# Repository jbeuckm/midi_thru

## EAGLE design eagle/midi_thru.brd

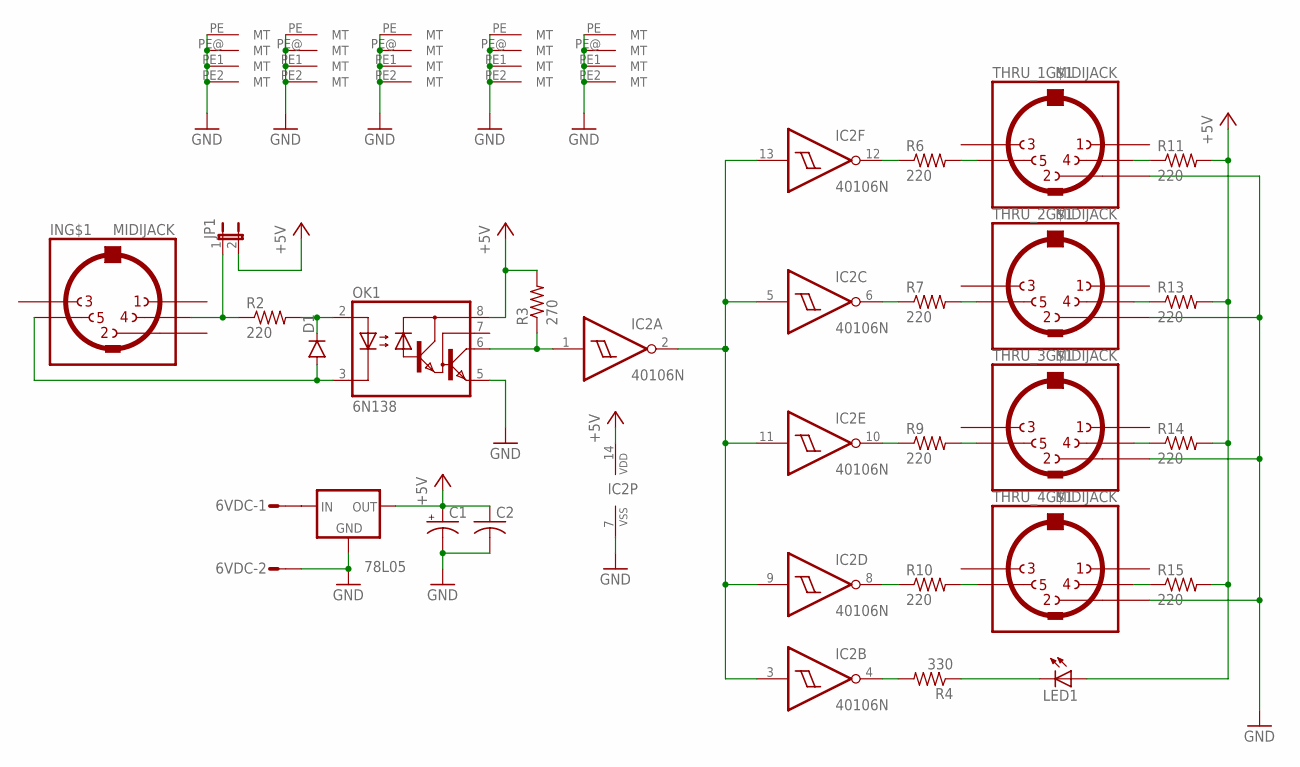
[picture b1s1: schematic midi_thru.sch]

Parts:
6VDC: S02P
78L05: 79LXX
C1: CPOL-USB45181A; B45181A
C2: C-US025-024X044; C025-024X044
D1: DIODE1N4148; DIODE-1N4148
IC2: 40106N; DIL14
IN: MIDIJACK; CP-2350
JP1: JP1E; JP1
LED1: LED5MM
OK1: 6N138; DIL08
R2, R6, R7, R9, R10, R11, R13, R14, R15: 220; 0207/7
R3: 270; 0207/7
R4: 330; 0207/7
THRU_1, THRU_2, THRU_3, THRU_4: MIDIJACK; CP-2350

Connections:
+5V: 78L05.OUT, C1.+, C2.1, IC2.14 (VDD), JP1.2, LED1.A, OK1.8 (VCC), R3.2, R11.2, R13.2, R14.2, R15.2
GND: 6VDC.2, 78L05.GND, C1.-, C2.2, IC2.7 (VSS), IN.PE (MT), IN.PE1 (MT), IN.PE2 (MT), IN.PE@ (MT), OK1.5 (GND), THRU_1.2, THRU_1.PE (MT), THRU_1.PE1 (MT), THRU_1.PE2 (MT), THRU_1.PE@ (MT), THRU_2.2, THRU_2.PE (MT), THRU_2.PE1 (MT), THRU_2.PE2 (MT), THRU_2.PE@ (MT), THRU_3.2, THRU_3.PE (MT), THRU_3.PE1 (MT), THRU_3.PE2 (MT), THRU_3.PE@ (MT), THRU_4.2, THRU_4.PE (MT), THRU_4.PE1 (MT), THRU_4.PE2 (MT), THRU_4.PE@ (MT)
unnamed: 6VDC.1, 78L05.IN
unnamed: IC2.4 (O), R4.2
unnamed: D1.A, IN.5, OK1.3 (C)
unnamed: LED1.K (C), R4.1
unnamed: IC2.8 (O), R10.1
unnamed: IN.4, JP1.1, R2.1
unnamed: D1.C, OK1.2 (A), R2.2
unnamed: IC2.10 (O), R9.1
unnamed: IC2.12 (O), R6.1
unnamed: IC2.2 (O), IC2.3 (I), IC2.5 (I), IC2.9 (I), IC2.11 (I), IC2.13 (I)
unnamed: IC2.6 (O), R7.1
unnamed: R6.2, THRU_1.5
unnamed: R7.2, THRU_2.5
unnamed: R9.2, THRU_3.5
unnamed: IC2.1 (I), OK1.6 (VO), R3.1
unnamed: R10.2, THRU_4.5
unnamed: R11.1, THRU_1.4
unnamed: R13.1, THRU_2.4
unnamed: R14.1, THRU_3.4
unnamed: R15.1, THRU_4.4

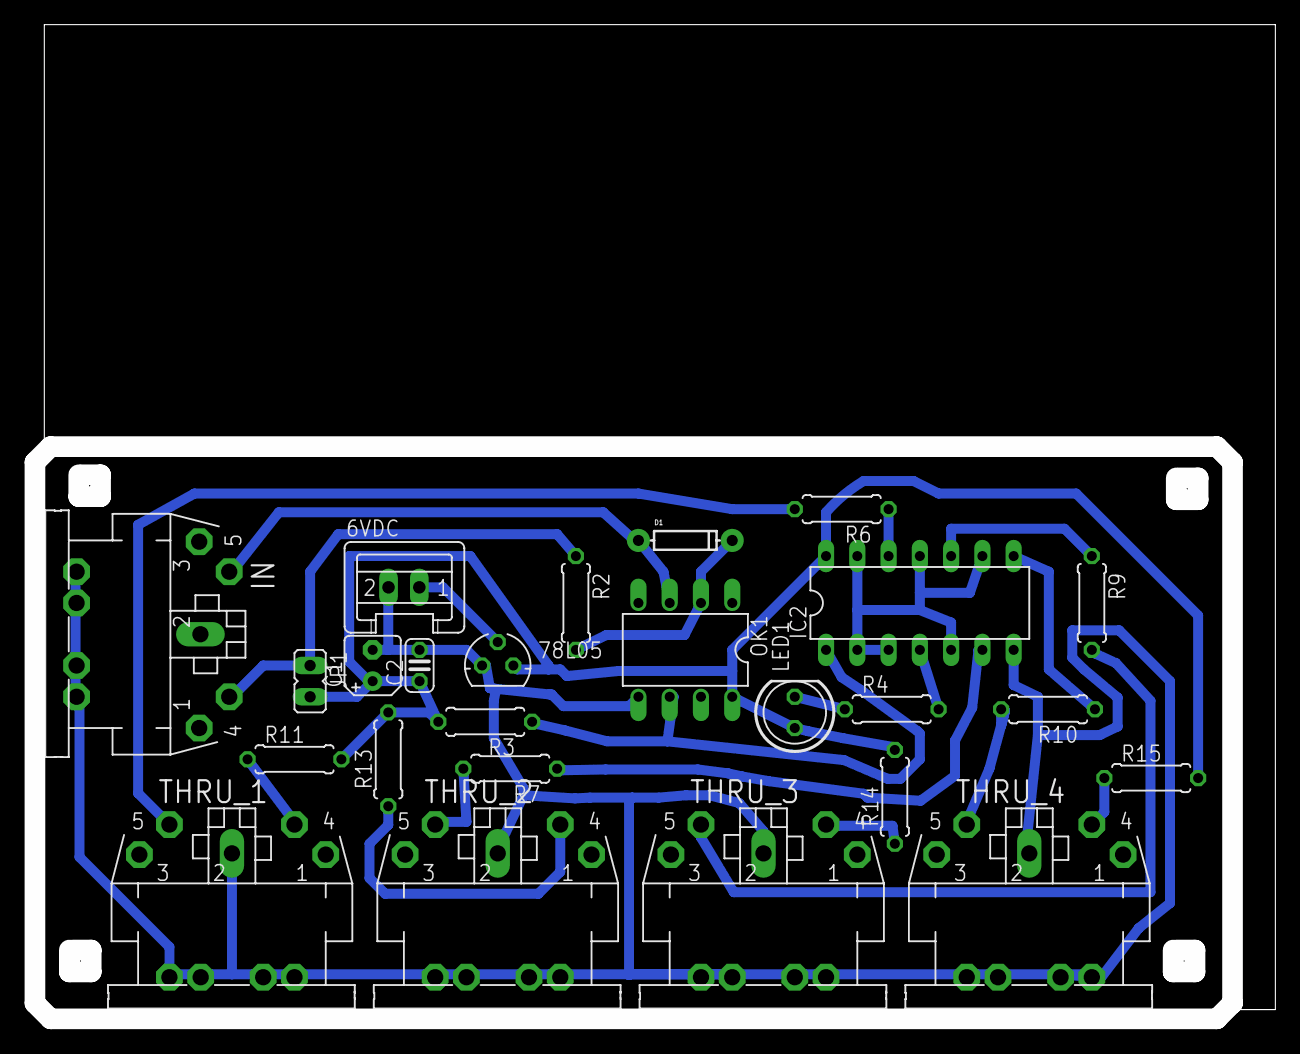
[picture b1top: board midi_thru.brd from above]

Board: 2 copper layers, 99.9 x 79.9 mm, 25 parts (0 on the bottom side), 22 nets.

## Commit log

2016-09-05 routed
2016-09-05 gcode first try
2016-09-11 first cut happened
2018-01-17 layout image
2018-01-17 Rename README.me to README.md
2018-01-18 draft of enclosure

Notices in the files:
parts and their libraries:
SparkFun-DiscreteSemi: Licensing: Creative Commons ShareAlike 4.0 International - https://creativecommons.org/licenses/by-sa/4.0
